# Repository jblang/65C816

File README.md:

# 65C816 Module for Elbert V2

This is a 65C816 module intended to plug into a Numato Elbert V2 FPGA board.  I had the board manufactured but never got around to developing the FGPA design. I am placing on GitHub as a backup in case I ever get back to it or in case anyone else wants to take it further.

## License

Copyright 2021 J.B. Langston

Permission is hereby granted, free of charge, to any person obtaining a copy of this software and associated documentation files (the "Software"), to deal in the Software without restriction, including without limitation the rights to use, copy, modify, merge, publish, distribute, sublicense, and/or sell copies of the Software, and to permit persons to whom the Software is furnished to do so, subject to the following conditions:

The above copyright notice and this permission notice shall be included in all copies or substantial portions of the Software.

THE SOFTWARE IS PROVIDED "AS IS", WITHOUT WARRANTY OF ANY KIND, EXPRESS OR IMPLIED, INCLUDING BUT NOT LIMITED TO THE WARRANTIES OF MERCHANTABILITY, FITNESS FOR A PARTICULAR PURPOSE AND NONINFRINGEMENT. IN NO EVENT SHALL THE AUTHORS OR COPYRIGHT HOLDERS BE LIABLE FOR ANY CLAIM, DAMAGES OR OTHER LIABILITY, WHETHER IN AN ACTION OF CONTRACT, TORT OR OTHERWISE, ARISING FROM, OUT OF OR IN CONNECTION WITH THE SOFTWARE OR THE USE OR OTHER DEALINGS IN THE SOFTWARE.

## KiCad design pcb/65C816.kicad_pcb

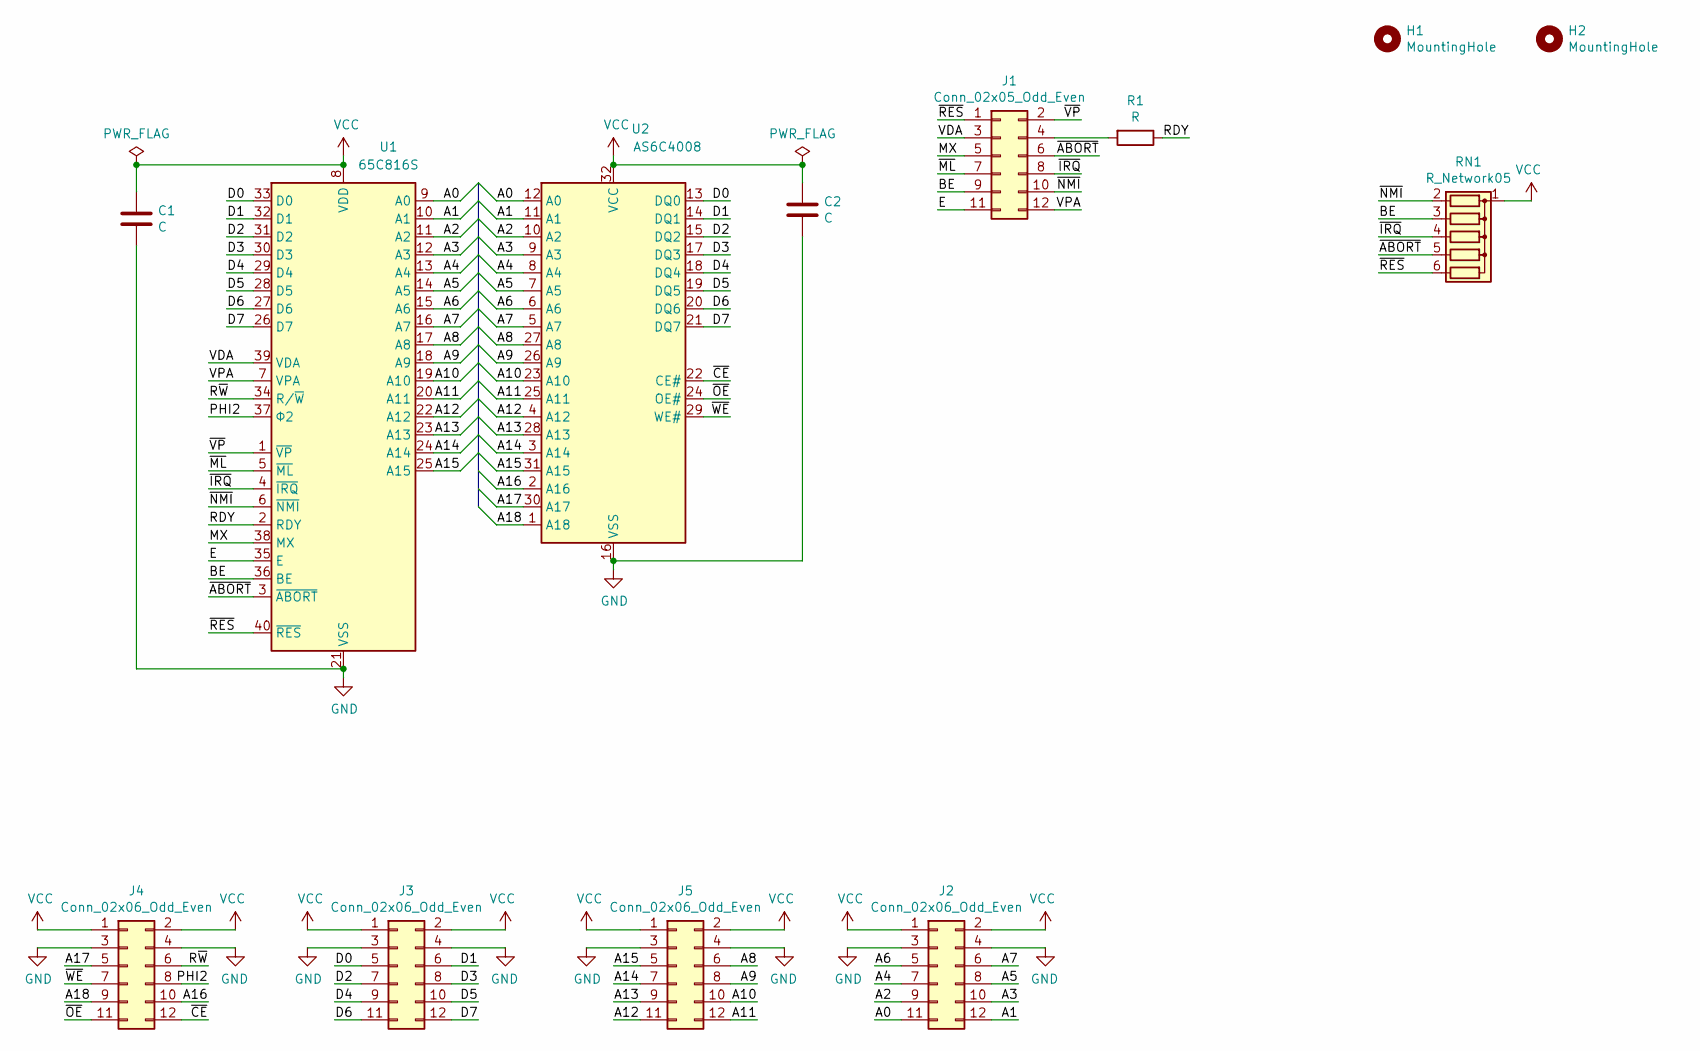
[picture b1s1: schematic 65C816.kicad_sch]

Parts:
C1, C2: C; C_Disc_D3.0mm_W1.6mm_P2.50mm
H1, H2: MountingHole; MountingHole_3.2mm_M3
J1: Conn_02x05_Odd_Even; PinHeader_2x06_P2.54mm_Vertical
J2, J3, J4, J5: Conn_02x06_Odd_Even; PinHeader_2x06_P2.54mm_Horizontal
R1: R; R_Axial_DIN0207_L6.3mm_D2.5mm_P7.62mm_Horizontal
RN1: R_Network05; R_Array_SIP6
U1: 65C816S; DIP-40_W15.24mm
U2: AS6C4008; DIP-32_W15.24mm

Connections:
/A0: J2.11, U1.9 (A0), U2.12 (A0)
/A1: J2.12, U1.10 (A1), U2.11 (A1)
/A2: J2.9, U1.11 (A2), U2.10 (A2)
/A3: J2.10, U1.12 (A3), U2.9 (A3)
/A4: J2.7, U1.13 (A4), U2.8 (A4)
/A5: J2.8, U1.14 (A5), U2.7 (A5)
/A6: J2.5, U1.15 (A6), U2.6 (A6)
/A7: J2.6, U1.16 (A7), U2.5 (A7)
/A8: J5.6, U1.17 (A8), U2.27 (A8)
/A9: J5.8, U1.18 (A9), U2.26 (A9)
/A10: J5.10, U1.19 (A10), U2.23 (A10)
/A11: J5.12, U1.20 (A11), U2.25 (A11)
/A12: J5.11, U1.22 (A12), U2.4 (A12)
/A13: J5.9, U1.23 (A13), U2.28 (A13)
/A14: J5.7, U1.24 (A14), U2.3 (A14)
/A15: J5.5, U1.25 (A15), U2.31 (A15)
/A16: J4.10, U2.2 (A16)
/A17: J4.5, U2.30 (A17)
/A18: J4.9, U2.1 (A18)
/BE: J1.9, RN1.3 (R2), U1.36 (BE)
/D0: J3.5, U1.33 (D0), U2.13 (DQ0)
/D1: J3.6, U1.32 (D1), U2.14 (DQ1)
/D2: J3.7, U1.31 (D2), U2.15 (DQ2)
/D3: J3.8, U1.30 (D3), U2.17 (DQ3)
/D4: J3.9, U1.29 (D4), U2.18 (DQ4)
/D5: J3.10, U1.28 (D5), U2.19 (DQ5)
/D6: J3.11, U1.27 (D6), U2.20 (DQ6)
/D7: J3.12, U1.26 (D7), U2.21 (DQ7)
/E: J1.11, U1.35 (E)
/MX: J1.5, U1.38 (MX)
/PHI2: J4.8, U1.37 (Φ2)
/RDY: R1.1, U1.2 (RDY)
/R~W: J4.6, U1.34 (R/~W)
/VDA: J1.3, U1.39 (VDA)
/VPA: J1.12, U1.7 (VPA)
/~ABORT: J1.6, RN1.5 (R4), U1.3 (~ABORT)
/~CE: J4.12, U2.22 (CE#)
/~IRQ: J1.8, RN1.4 (R3), U1.4 (~IRQ)
/~ML: J1.7, U1.5 (~ML)
/~NMI: J1.10, RN1.2 (R1), U1.6 (~NMI)
/~OE: J4.11, U2.24 (OE#)
/~RES: J1.1, RN1.6 (R5), U1.40 (~RES)
/~VP: J1.2, U1.1 (~VP)
/~WE: J4.7, U2.29 (WE#)
GND: C1.2, C2.2, J2.3, J2.4, J3.3, J3.4, J4.3, J4.4, J5.3, J5.4, U1.21 (VSS), U2.16 (VSS)
unnamed: J1.4, R1.2
VCC: C1.1, C2.1, J2.1, J2.2, J3.1, J3.2, J4.1, J4.2, J5.1, J5.2, RN1.1 (common), U1.8 (VDD), U2.32 (VCC)

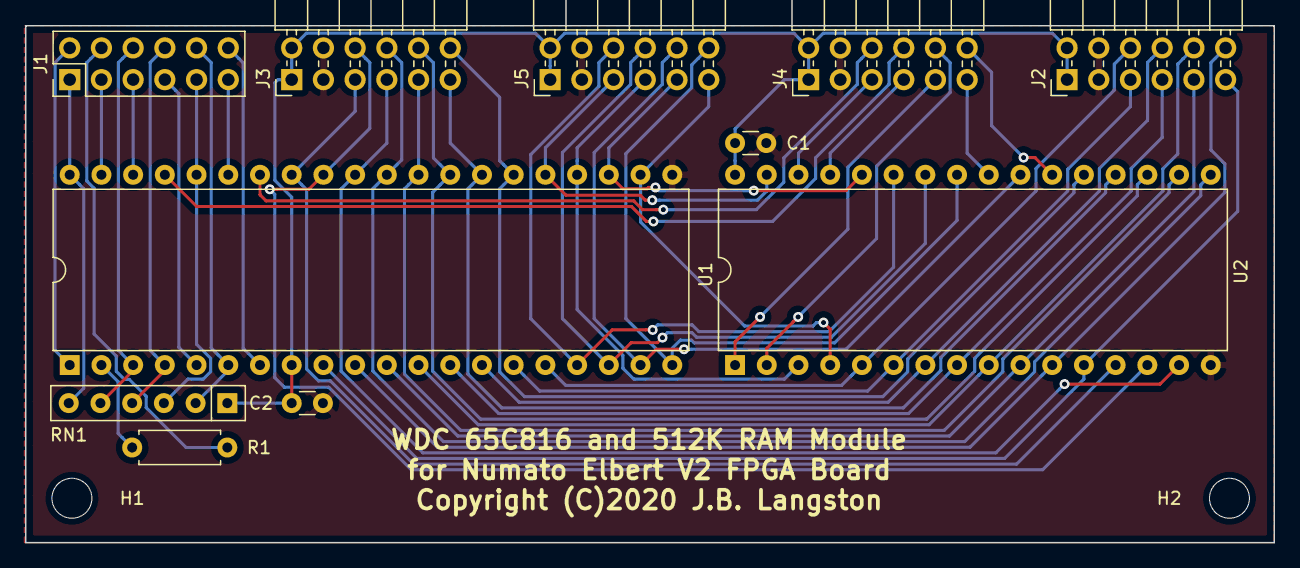
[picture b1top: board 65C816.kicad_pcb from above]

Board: 2 copper layers, 100.0 x 41.4 mm, 13 parts (0 on the bottom side), 47 nets.

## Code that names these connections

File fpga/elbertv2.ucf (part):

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    NET "OE"           LOC = P21   | IOSTANDARD = LVCMOS33 | SLEW = SLOW | DRIVE = 12;
    NET "ADDR[16]"           LOC = P18   | IOSTANDARD = LVCMOS33 | SLEW = SLOW | DRIVE = 12;
    NET "ADDR[18]"           LOC = P20   | IOSTANDARD = LVCMOS33 | SLEW = SLOW | DRIVE = 12;
    NET "PHI2"           LOC = P15   | IOSTANDARD = LVCMOS33 | SLEW = SLOW | DRIVE = 12;
    NET "WE"           LOC = P16   | IOSTANDARD = LVCMOS33 | SLEW = SLOW | DRIVE = 12;
    NET "RW"           LOC = P12   | IOSTANDARD = LVCMOS33 | SLEW = SLOW | DRIVE = 12;
    NET "ADDR[17]"           LOC = P13   | IOSTANDARD = LVCMOS33 | SLEW = SLOW | DRIVE = 12;
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# HEADER P5
# Two input PINs of P5 Header IO_P5[1] and IO_P5[7]. 
    
    NET "RES"           LOC = P125  | IOSTANDARD = LVCMOS33 | SLEW = SLOW | DRIVE = 12;
    NET "IO_P5[1]"           LOC = P123  | IOSTANDARD = LVCMOS33 | SLEW = SLOW | DRIVE = 12 | PULLUP;
    NET "BE"           LOC = P127  | IOSTANDARD = LVCMOS33 | SLEW = SLOW | DRIVE = 12;
    NET "IO_P5[3]"           LOC = P126  | IOSTANDARD = LVCMOS33 | SLEW = SLOW | DRIVE = 12;
    NET "RDY"           LOC = P131  | IOSTANDARD = LVCMOS33 | SLEW = SLOW | DRIVE = 12;
    NET "IO_P5[5]"           LOC = P91   | IOSTANDARD = LVCMOS33 | SLEW = SLOW | DRIVE = 12;
    NET "IRQ"           LOC = P142  | IOSTANDARD = LVCMOS33 | SLEW = SLOW | DRIVE = 12;
    NET "IO_P5[7]"           LOC = P140  | IOSTANDARD = LVCMOS33 | SLEW = SLOW | DRIVE = 12 | PULLUP;   
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
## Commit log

2022-10-22 Upgrade Kicad projects to v6

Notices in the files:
pcb/65C816.kicad_pcb:
Copyright (C)2020 J.B. Langston
